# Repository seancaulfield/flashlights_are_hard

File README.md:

flashlights_are_hard
====================

My primative attempts to design a flashlight that has more complicated features
than ON/OFF without completely pissing me off.

Unless otherwise specified, everything here is licensed under the Creative
Commons Attribution-ShareAlike License.

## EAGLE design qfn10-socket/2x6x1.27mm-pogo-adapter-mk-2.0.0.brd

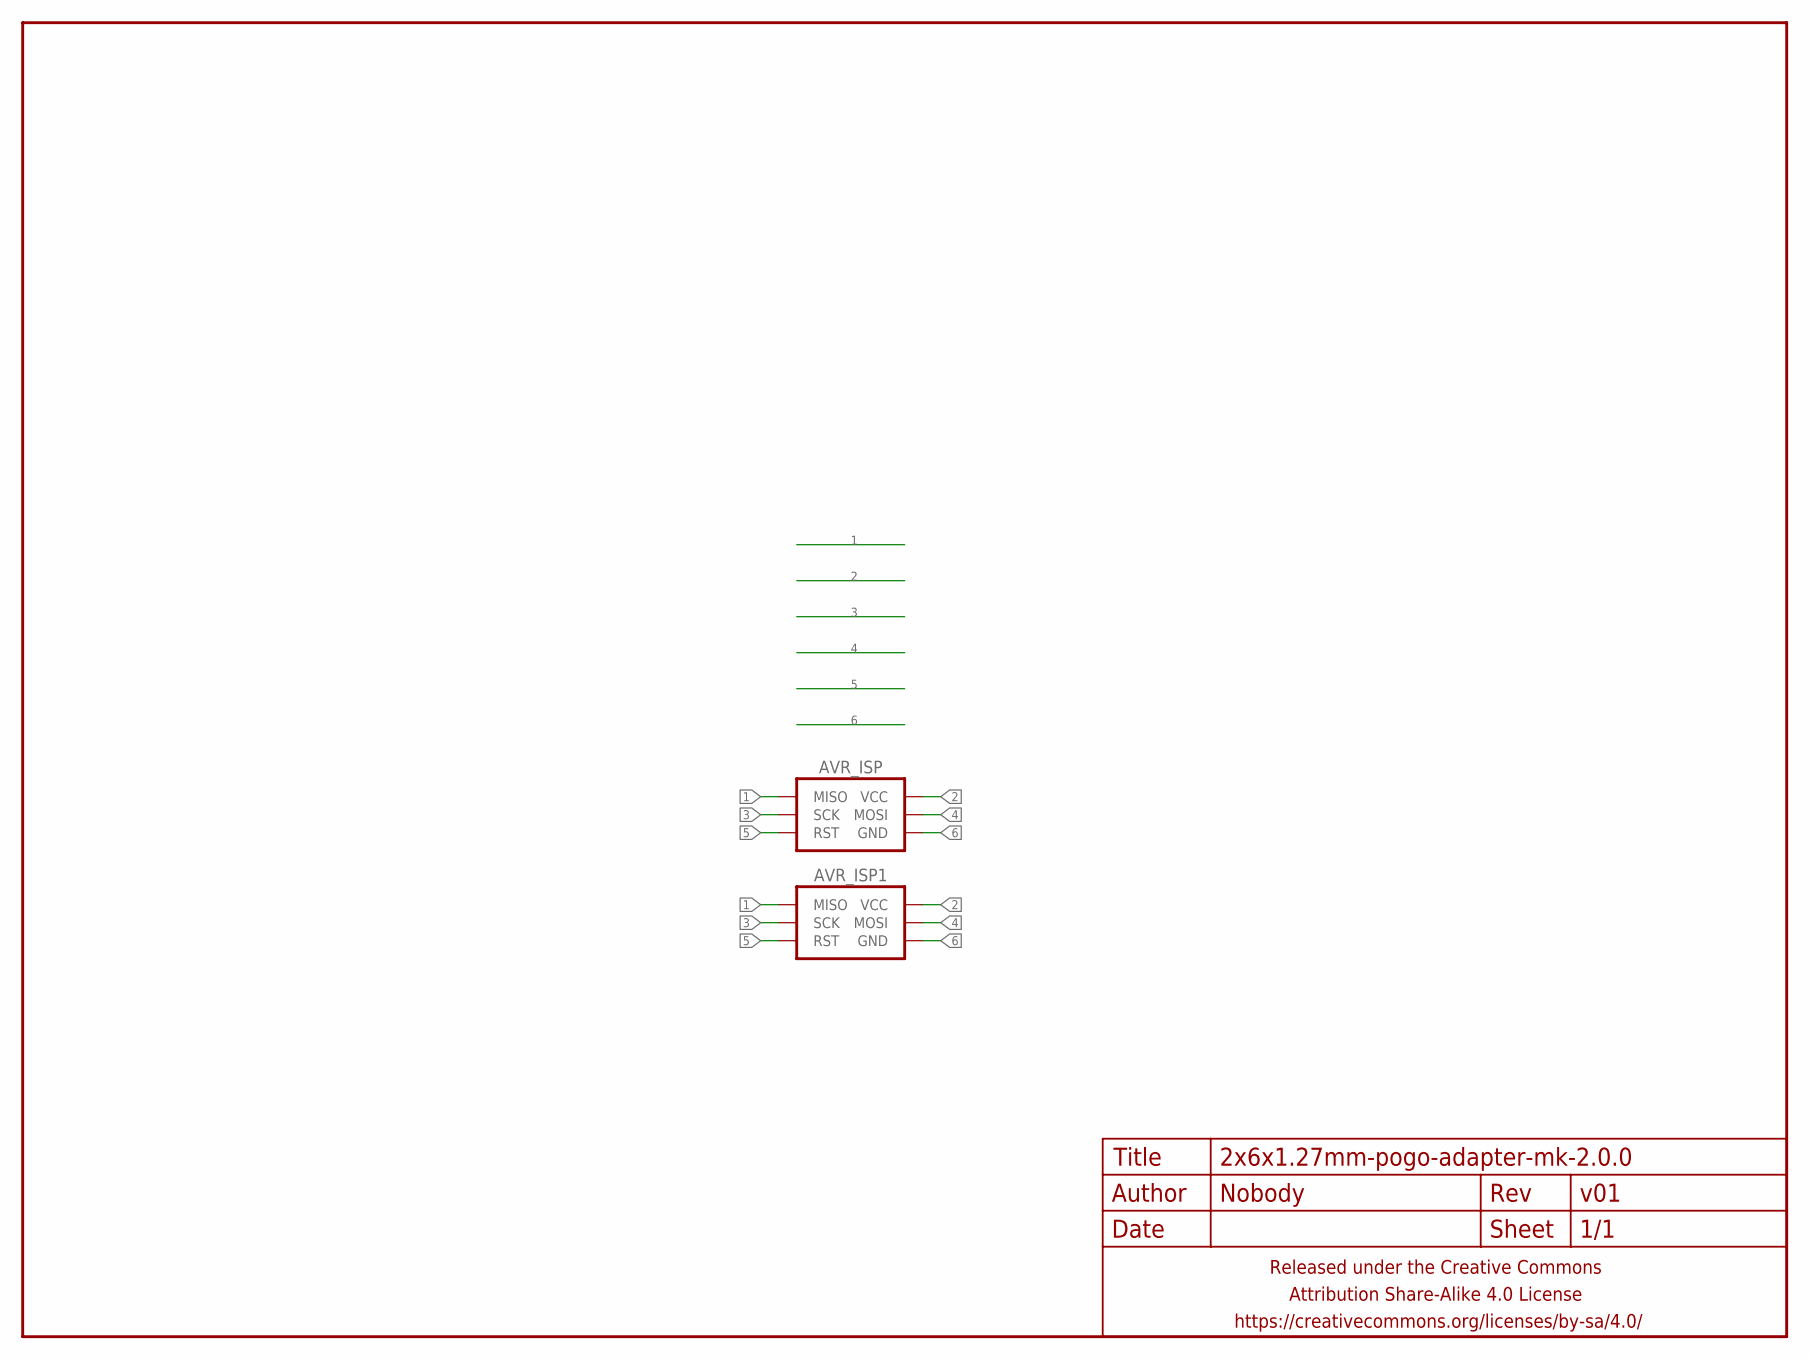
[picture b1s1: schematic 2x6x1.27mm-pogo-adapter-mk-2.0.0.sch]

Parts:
AVR_ISP: AVR_SPI_PRG_6SMD_POGO_POGO_POGO_BOUNCE_AVRISP; 2X3_SMD_POGO_RA_NARROW_AVRISP
AVR_ISP1: AVR_SPI_PRG_6PTH; 2X3
FRAME1: FRAME-LETTERNO_PACKAGE; DUMMY

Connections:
1: AVR_ISP.1@1 (MISO), AVR_ISP.1@2 (MISO), AVR_ISP1.1 (MISO)
2: AVR_ISP.2@1 (VCC), AVR_ISP.2@2 (VCC), AVR_ISP1.2 (VCC)
3: AVR_ISP.3@1 (SCK), AVR_ISP.3@2 (SCK), AVR_ISP1.3 (SCK)
4: AVR_ISP.4@1 (MOSI), AVR_ISP.4@2 (MOSI), AVR_ISP1.4 (MOSI)
5: AVR_ISP.5@1 (RST), AVR_ISP.5@2 (RST), AVR_ISP1.5 (RST)
6: AVR_ISP.6@1 (GND), AVR_ISP.6@2 (GND), AVR_ISP1.6 (GND)

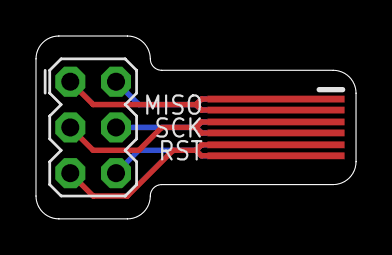
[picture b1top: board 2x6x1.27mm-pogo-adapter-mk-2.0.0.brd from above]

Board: 2 copper layers, 17.8 x 10.2 mm, 3 parts (0 on the bottom side), 6 nets.

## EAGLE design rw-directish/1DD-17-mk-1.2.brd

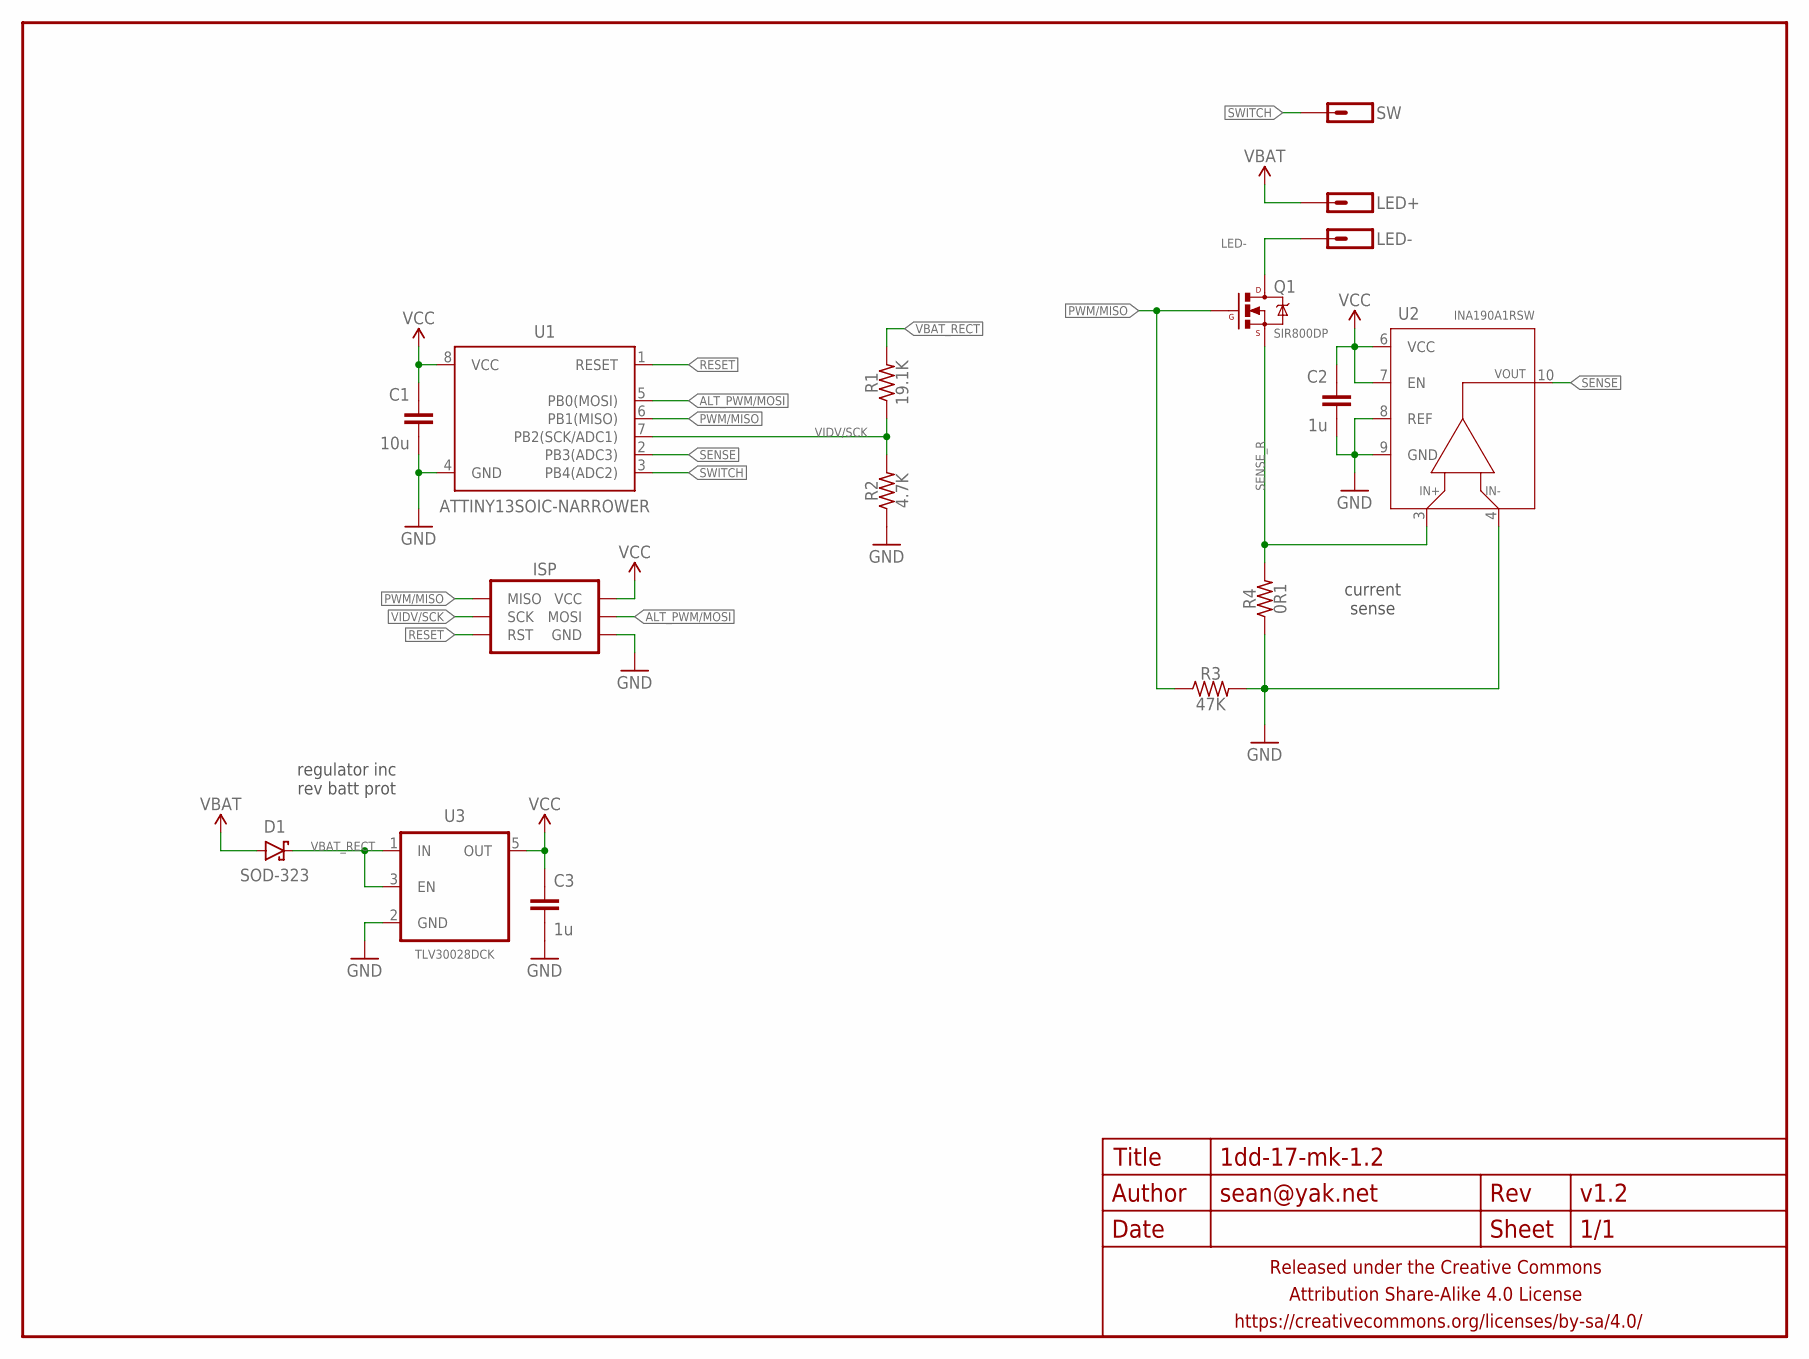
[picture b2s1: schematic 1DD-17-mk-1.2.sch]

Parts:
C1: 10u; C0402
C2, C3: 1u; C0402
D1: SOD-323; SOD323-SCHOTTKY
FRAME1: FRAME-LETTERNO_PACKAGE; DUMMY
ISP: AVR_SPI_PRG_6SMD-1.27MM; 2X3-1.27MM-SMD
LED+: M01PTH-0.9MM-CIR; 1X01-0.9MM-CIR
LED-: M01PTH-0.9MM-CIR; 1X01-0.9MM-CIR
Q1: SIR800DP; LFPAK56
R1: 19.1K; R0402
R2: 4.7K; R0402
R3: 47K; R0402
R4: 0R1; R0805-TIGHTER
SW: M01SMD-1MM-DIA-NS; 1X01-SMD-1MM-DIA-NS
U1: ATTINY13SOIC-NARROWER; SO08-SKINNYPADS
U2: INA190A1RSW; UQFN-10
U3: TLV30028DCK; SC70-TIGHTER

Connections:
ALT_PWM/MOSI: ISP.4 (MOSI), U1.5 (PB0(MOSI))
GND: C1.2, C2.2, C3.2, ISP.6 (GND), R2.1, R3.2, R4.1, U1.4 (GND), U2.4 (VIN-), U2.8 (REF), U2.9 (GND), U3.2 (GND)
LED-: LED-.P$1, Q1.PAD (D)
PWM/MISO: ISP.1 (MISO), Q1.4 (G), R3.1, U1.6 (PB1(MISO))
RESET: ISP.5 (RST), U1.1 (RESET)
SENSE: U1.2 (PB3(ADC3)), U2.10 (OUT)
SENSE_R: Q1.1 (S), Q1.2 (S), Q1.3 (S), R4.2, U2.3 (VIN+)
SWITCH: SW.P$1, U1.3 (PB4(ADC2))
VBAT: D1.A, LED+.P$1
VBAT_RECT: D1.C, R1.2, U3.1 (IN), U3.3 (EN)
VCC: C1.1, C2.1, C3.1, ISP.2 (VCC), U1.8 (VCC), U2.6 (VCC), U2.7 (EN), U3.5 (OUT)
VIDV/SCK: ISP.3 (SCK), R1.1, R2.2, U1.7 (PB2(SCK/ADC1))

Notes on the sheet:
current sense
regulator inc rev batt prot

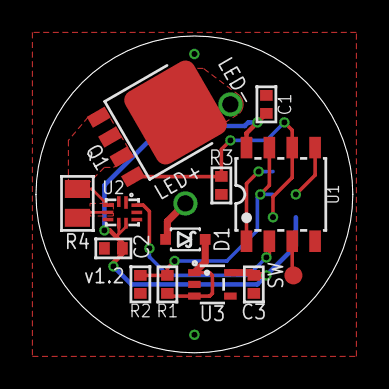
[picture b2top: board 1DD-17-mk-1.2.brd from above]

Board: 2 copper layers, 17.6 x 17.6 mm, 17 parts (1 on the bottom side), 12 nets.

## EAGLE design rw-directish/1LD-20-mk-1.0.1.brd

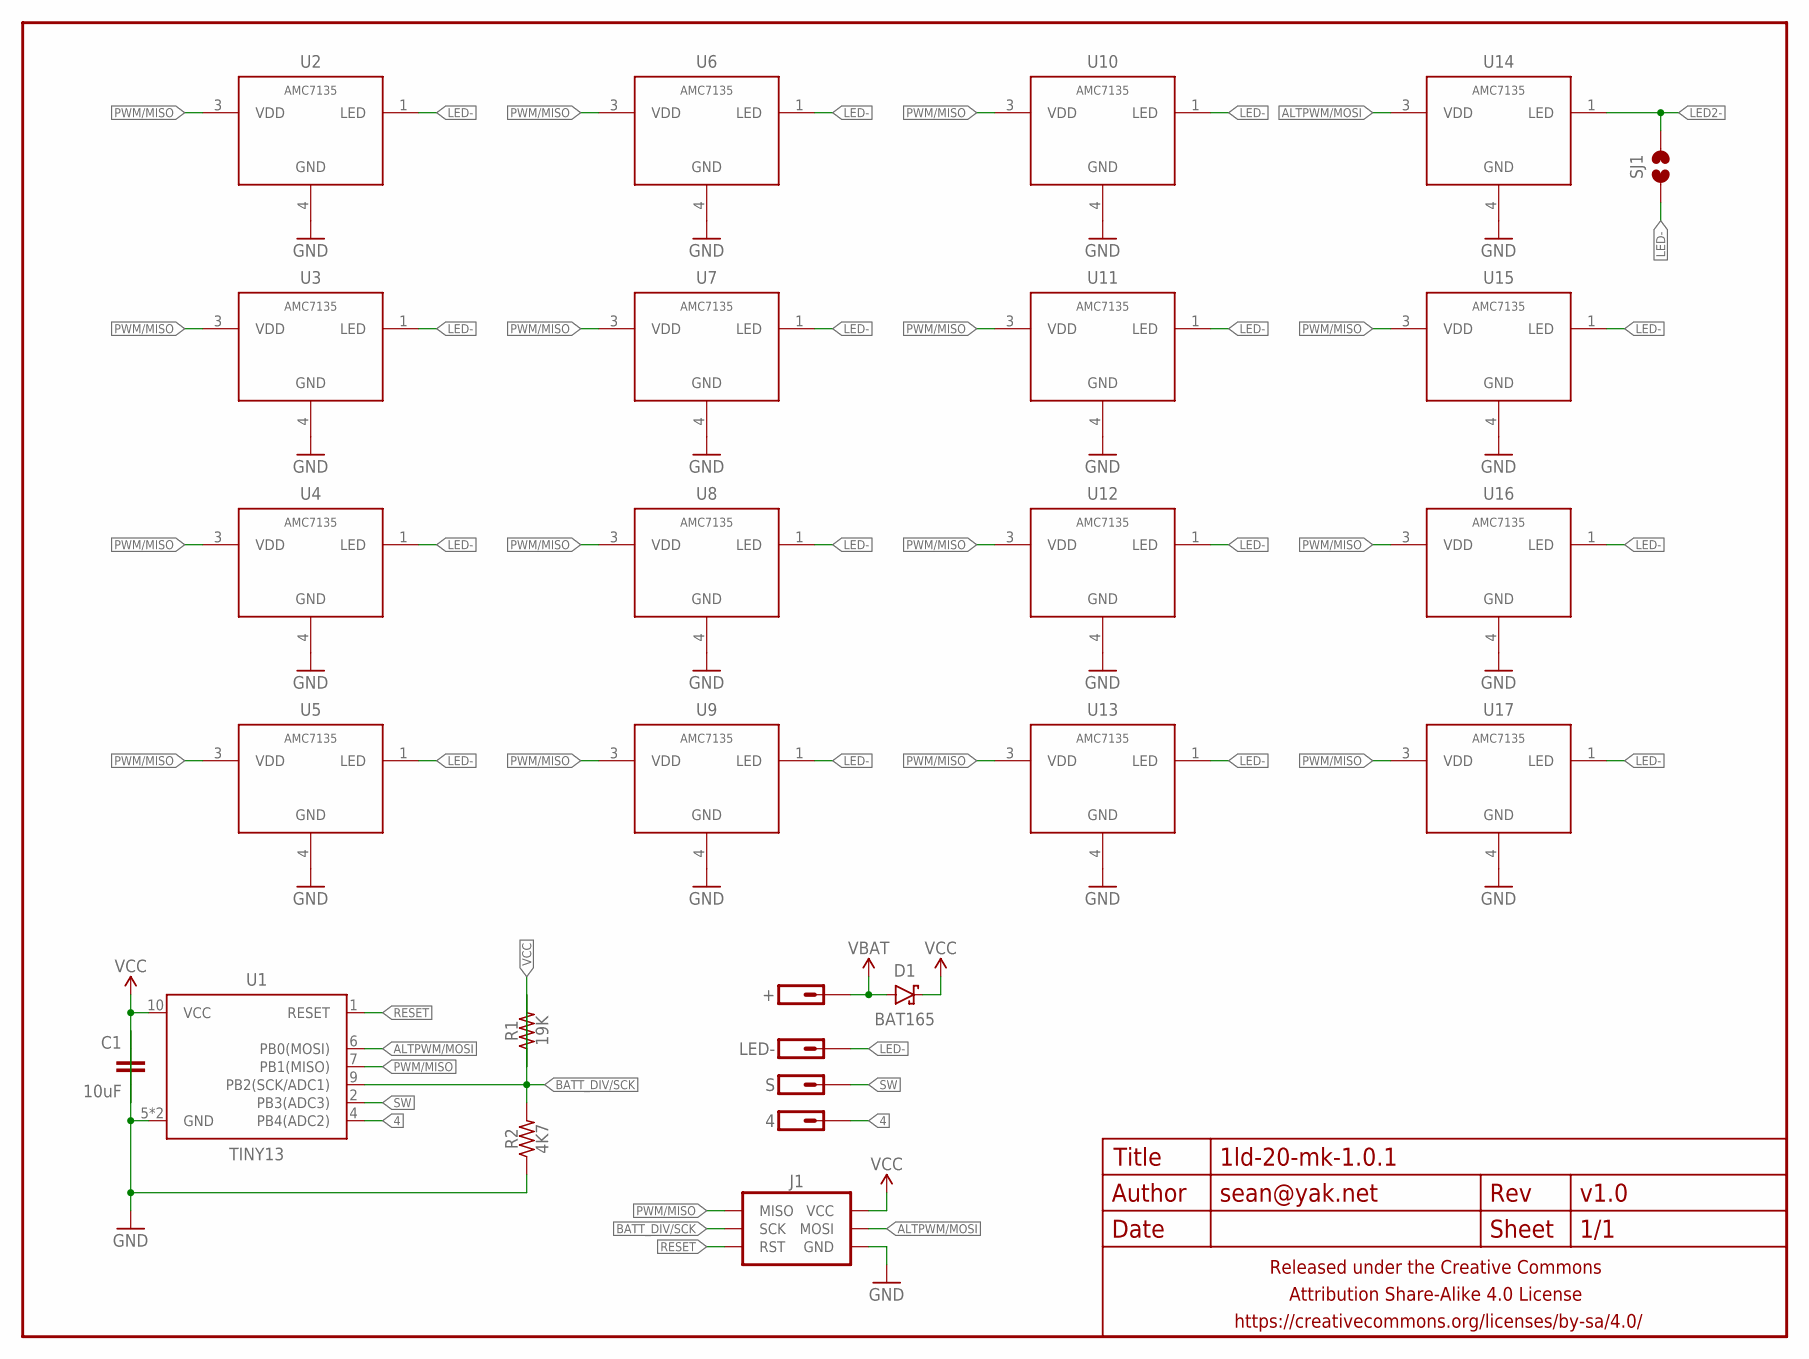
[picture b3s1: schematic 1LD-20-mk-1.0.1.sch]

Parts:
4: M01SMD-1MM-DIA-NS; 1X01-SMD-1MM-DIA-NS
+: M01PTH-1.4MM; 1X01-1.4MM-CIR
C1: 10uF; C0402
D1: BAT165; SOD323-SCHOTTKY
FRAME1: FRAME-LETTERNO_PACKAGE; DUMMY
J1: AVR_SPI_PRG_6SMD-1.27MM; 2X3-1.27MM-SMD
LED-: M01PTH-1MM-CIR-NS; 1X01-1MM-CIR-NS
R1: 19K; R0402
R2: 4K7; R0402
S: M01SMD-1MM-DIA-NS; 1X01-SMD-1MM-DIA-NS
SJ1: JUMPER-PAD-2-NOSMOL_NS; PAD-JUMPER-2-NO_SMOL_NS
U1: TINY13; QFN10(2X5)
U2, U3, U4, U5, U6, U7, U8, U9, U10, U11, U12, U13, U14, U15, U16, U17: AMC7135; SOT89-NOTHERM-ROUNDED-LESS

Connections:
4: 4.P$1, U1.4 (PB4(ADC2))
ALTPWM/MOSI: J1.4 (MOSI), U1.6 (PB0(MOSI)), U14.3 (VDD)
BATT_DIV/SCK: J1.3 (SCK), R1.2, R2.2, U1.9 (PB2(SCK/ADC1))
GND: C1.1, J1.6 (GND), R2.1, U1.5 (GND), U1.PAD (GND), U2.4 (GND), U3.4 (GND), U4.4 (GND), U5.4 (GND), U6.4 (GND), U7.4 (GND), U8.4 (GND), U9.4 (GND), U10.4 (GND), U11.4 (GND), U12.4 (GND), U13.4 (GND), U14.4 (GND), U15.4 (GND), U16.4 (GND), U17.4 (GND)
LED2-: SJ1.2, U14.1 (LED)
LED-: LED-.1, SJ1.1, U2.1 (LED), U3.1 (LED), U4.1 (LED), U5.1 (LED), U6.1 (LED), U7.1 (LED), U8.1 (LED), U9.1 (LED), U10.1 (LED), U11.1 (LED), U12.1 (LED), U13.1 (LED), U15.1 (LED), U16.1 (LED), U17.1 (LED)
PWM/MISO: J1.1 (MISO), U1.7 (PB1(MISO)), U2.3 (VDD), U3.3 (VDD), U4.3 (VDD), U5.3 (VDD), U6.3 (VDD), U7.3 (VDD), U8.3 (VDD), U9.3 (VDD), U10.3 (VDD), U11.3 (VDD), U12.3 (VDD), U13.3 (VDD), U15.3 (VDD), U16.3 (VDD), U17.3 (VDD)
RESET: J1.5 (RST), U1.1 (RESET)
SW: S.P$1, U1.2 (PB3(ADC3))
VBAT: +.P$1, D1.A
VCC: C1.2, D1.C, J1.2 (VCC), R1.1, U1.10 (VCC)

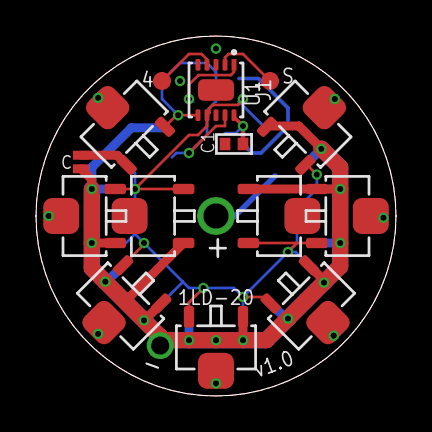
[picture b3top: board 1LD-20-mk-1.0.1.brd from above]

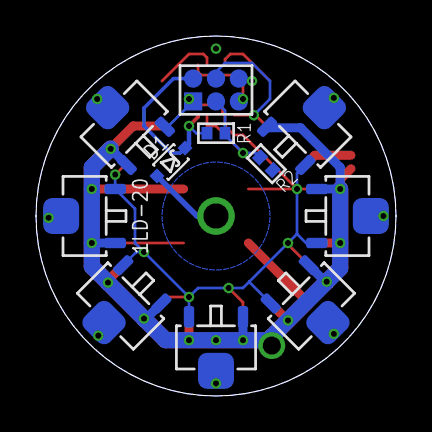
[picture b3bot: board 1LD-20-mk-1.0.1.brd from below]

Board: 2 copper layers, 20.0 x 20.0 mm, 28 parts (11 on the bottom side), 11 nets.

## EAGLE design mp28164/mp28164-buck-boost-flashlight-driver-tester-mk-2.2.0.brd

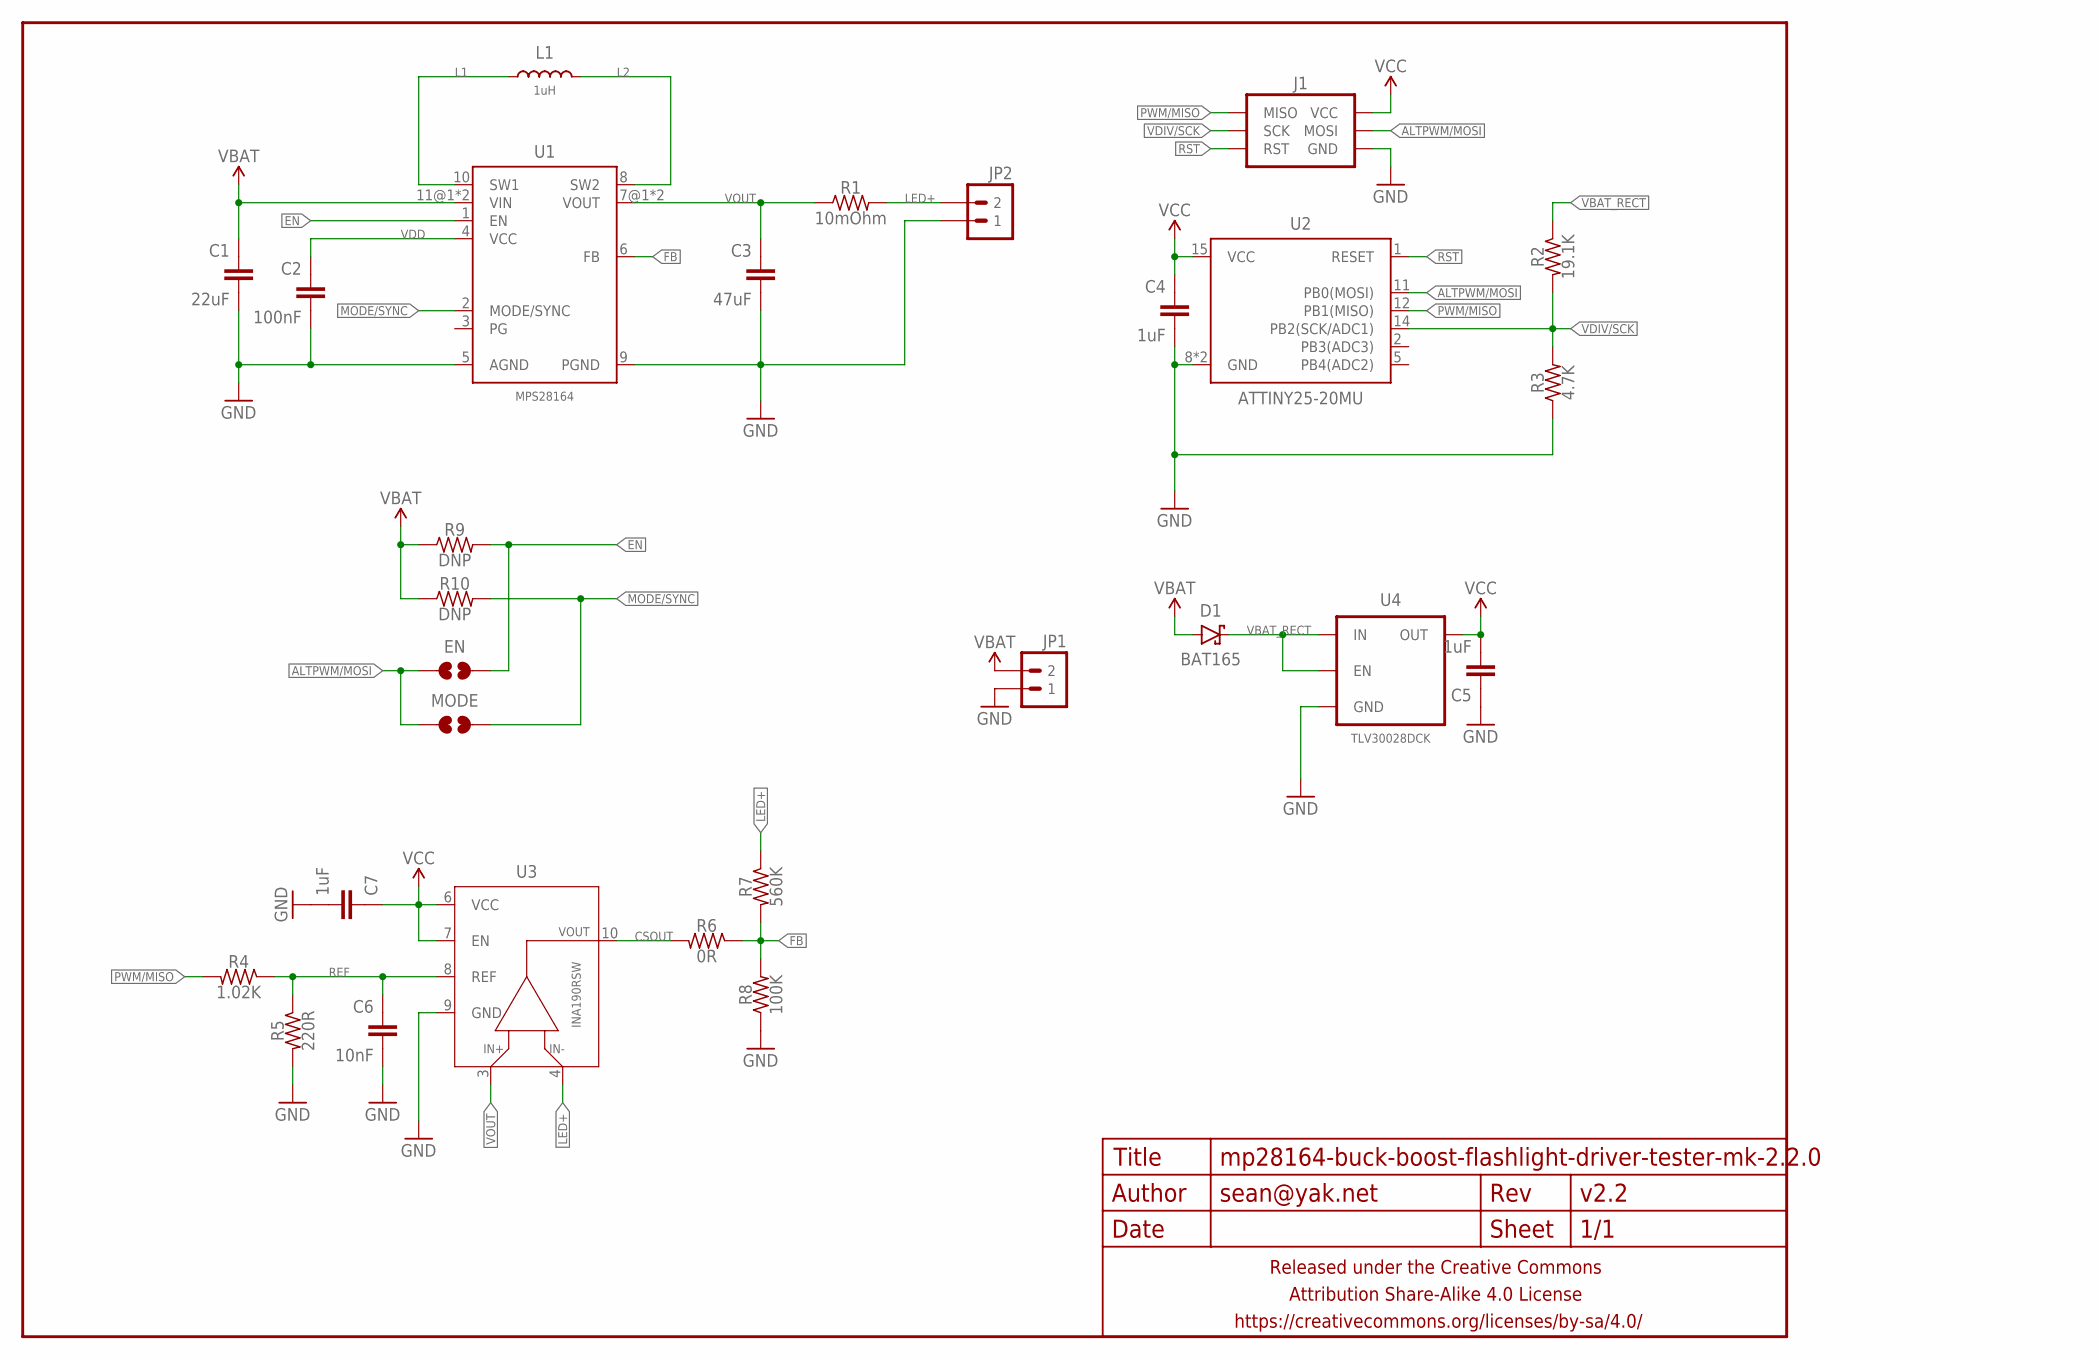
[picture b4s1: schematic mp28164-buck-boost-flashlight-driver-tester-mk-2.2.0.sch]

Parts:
C1: 22uF; C1206
C2: 100nF; C0402
C3: 47uF; C1206
C4, C5, C7: 1uF; C0402
C6: 10nF; C0402
D1: BAT165; SOD323-SCHOTTKY
EN: JUMPER-PAD-2-NOYES_SILK; PAD-JUMPER-2-NO_YES_SILK
FRAME1: FRAME-LETTERNO_PACKAGE; DUMMY
J1: AVR_SPI_PRG_6PTH; 2X3
JP1, JP2: M021X02_NO_SILK; 1X02_NO_SILK
L1: 1uH; XAL60XX
MODE: JUMPER-PAD-2-NOYES_SILK; PAD-JUMPER-2-NO_YES_SILK
R1: 10mOhm; R1206
R2: 19.1K; R0402
R3: 4.7K; R0402
R4: 1.02K; R0402
R5: 220R; R0402
R6: 0R; R0402
R7: 560K; R0402
R8: 100K; R0402
R9, R10: DNP; R0402
U1: MPS28164
U2: ATTINY25-20MU; QFN20
U3: INA190RSW; UQFN-10
U4: TLV30028DCK; SC70-TIGHTER

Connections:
ALTPWM/MOSI: EN.1, J1.4 (MOSI), MODE.1, U2.11 (PB0(MOSI))
CSOUT: R6.2, U3.10 (OUT)
EN: EN.2, R9.2, U1.1 (EN)
FB: R6.1, R7.2, R8.2, U1.6 (FB)
GND: C1.2, C2.2, C3.2, C4.2, C5.1, C6.2, C7.2, J1.6 (GND), JP1.1, JP2.1, R3.1, R5.2, R8.1, U1.5 (AGND), U1.9 (PGND), U2.8 (GND), U2.PAD (GND), U3.9 (GND), U4.2 (GND)
L1: L1.P$1 (1), U1.10 (SW1)
L2: L1.P$2 (2), U1.8 (SW2)
LED+: JP2.2, R1.2, R7.1, U3.4 (VIN-)
MODE/SYNC: MODE.2, R10.2, U1.2 (MODE/SYNC)
PWM/MISO: J1.1 (MISO), R4.2, U2.12 (PB1(MISO))
REF: C6.1, R4.1, R5.1, U3.8 (REF)
RST: J1.5 (RST), U2.1 (RESET)
VBAT: C1.1, D1.A, JP1.2, R9.1, R10.1, U1.11@1 (VIN), U1.11@2 (VIN)
VBAT_RECT: D1.C, R2.1, U4.1 (IN), U4.3 (EN)
VCC: C4.1, C5.2, C7.1, J1.2 (VCC), U2.15 (VCC), U3.6 (VCC), U3.7 (EN), U4.5 (OUT)
VDD: C2.1, U1.4 (VCC)
VDIV/SCK: J1.3 (SCK), R2.2, R3.2, U2.14 (PB2(SCK/ADC1))
VOUT: C3.1, R1.1, U1.7@1 (VOUT), U1.7@2 (VOUT), U3.3 (VIN+)

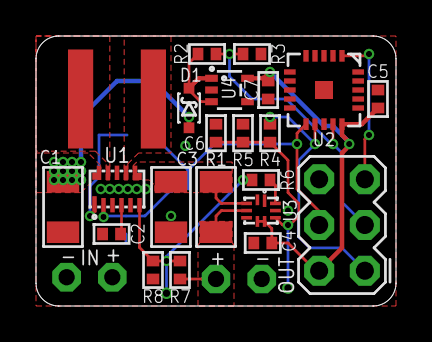
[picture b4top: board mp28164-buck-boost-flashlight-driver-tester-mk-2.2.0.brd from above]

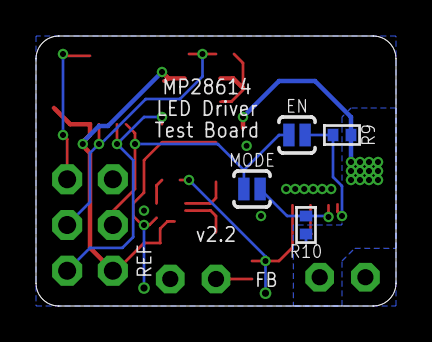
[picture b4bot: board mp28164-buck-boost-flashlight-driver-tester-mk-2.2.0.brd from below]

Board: 2 copper layers, 20.0 x 15.0 mm, 29 parts (4 on the bottom side), 18 nets.

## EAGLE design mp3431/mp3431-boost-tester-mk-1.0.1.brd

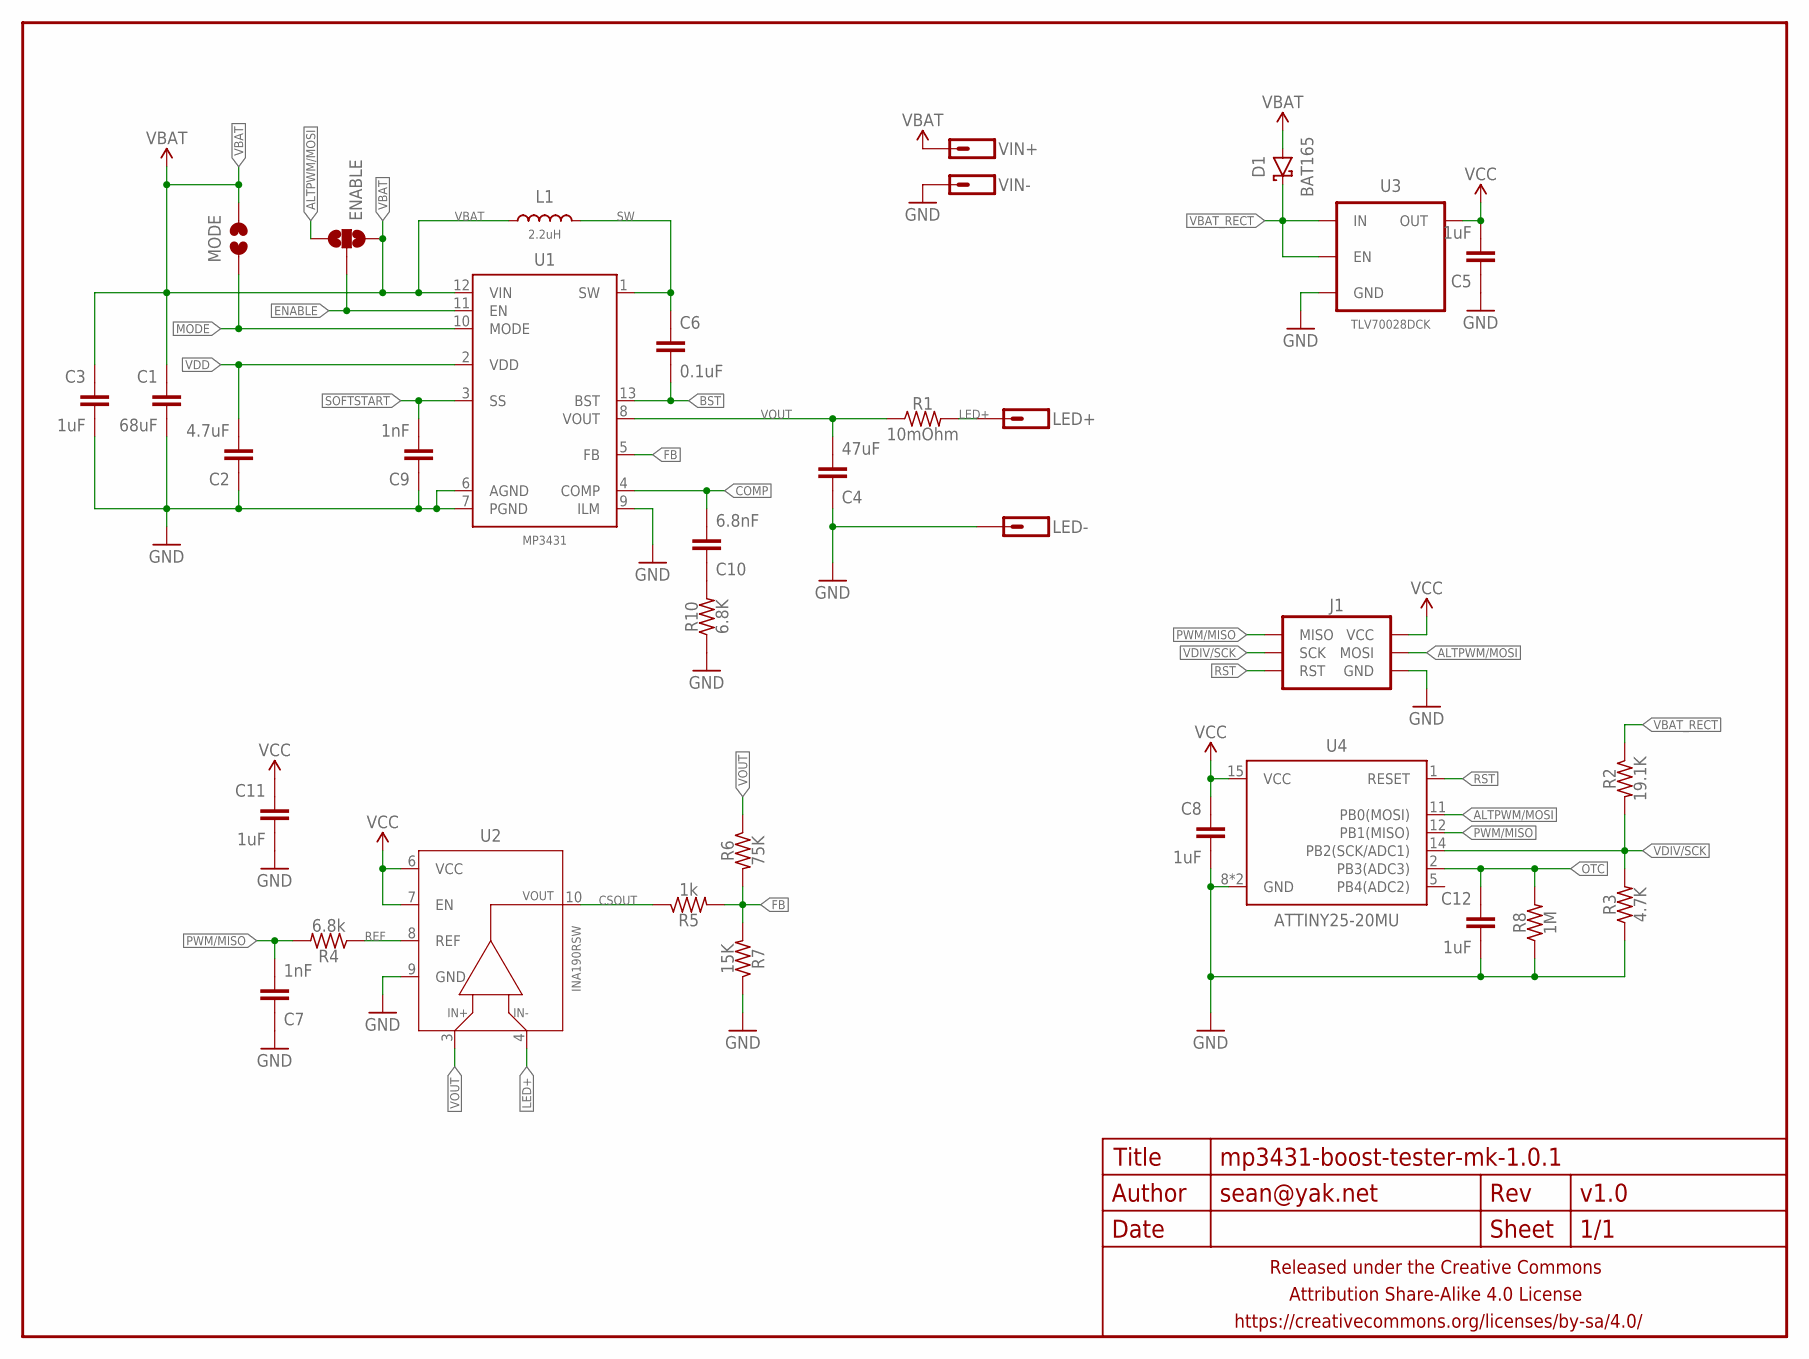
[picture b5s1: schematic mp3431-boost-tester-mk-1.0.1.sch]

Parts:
C1: 68uF; C1210
C2: 4.7uF; C0402
C3, C5, C8, C11, C12: 1uF; C0402
C4: 47uF; C1210
C6: 0.1uF; C0402
C7, C9: 1nF; C0402
C10: 6.8nF; C0402
D1: BAT165; SOD323-SCHOTTKY
ENABLE: JUMPER-PAD-3-NOSMALL_BOX_SILK; PAD-JUMPER-3-NO_YES_SILK_SMALL_BOX
FRAME1: FRAME-LETTERNO_PACKAGE; DUMMY
J1: AVR_SPI_PRG_6PTH; 2X3
L1: 2.2uH; XAL7070
LED+: M01PTH-1.2MM-NS; 1X01-1.2MM-NS
LED-: M01PTH-1.2MM-NS; 1X01-1.2MM-NS
MODE: JUMPER-PAD-2-NOYES_SILK; PAD-JUMPER-2-NO_YES_SILK
R1: 10mOhm; R1206
R2: 19.1K; R0402
R3: 4.7K; R0402
R4: 6.8k; R0402
R5: 1k; R0402
R6: 75K; R0402
R7: 15K; R0402
R8: 1M; R0402
R10: 6.8K; R0402
U1: MP3431
U2: INA190RSW; UQFN-10
U3: TLV70028DCK; SC70
U4: ATTINY25-20MU; QFN20
VIN+: M01PTH-1.2MM-NS; 1X01-1.2MM-NS
VIN-: M01PTH-1.2MM-NS; 1X01-1.2MM-NS

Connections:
ALTPWM/MOSI: ENABLE.3, J1.4 (MOSI), U4.11 (PB0(MOSI))
BST: C6.2, U1.13 (BST)
COMP: C10.2, U1.4 (COMP)
COMP_MID: C10.1, R10.2
CSOUT: R5.1, U2.10 (OUT)
ENABLE: ENABLE.2, U1.11 (EN)
FB: R5.2, R6.2, R7.2, U1.5 (FB)
GND: C1.2, C2.1, C3.2, C4.1, C5.1, C7.1, C8.2, C9.1, C11.2, C12.2, J1.6 (GND), LED-.P$1, R3.1, R7.1, R8.1, R10.1, U1.6 (AGND), U1.7 (PGND), U1.9 (ILM), U2.9 (GND), U3.2 (GND), U4.8 (GND), U4.PAD (GND), VIN-.P$1
LED+: LED+.P$1, R1.2, U2.4 (VIN-)
MODE: MODE.1, U1.10 (MODE)
OTC: C12.1, R8.2, U4.2 (PB3(ADC3))
PWM/MISO: C7.2, J1.1 (MISO), R4.2, U4.12 (PB1(MISO))
REF: R4.1, U2.8 (REF)
RST: J1.5 (RST), U4.1 (RESET)
SOFTSTART: C9.2, U1.3 (SS)
SW: C6.1, L1.P$2 (2), U1.1 (SW)
VBAT: C1.1, C3.1, D1.A, ENABLE.1, L1.P$1 (1), MODE.2, U1.12 (VIN), VIN+.P$1
VBAT_RECT: D1.C, R2.1, U3.1 (IN), U3.3 (EN)
VCC: C5.2, C8.1, C11.1, J1.2 (VCC), U2.6 (VCC), U2.7 (EN), U3.5 (OUT), U4.15 (VCC)
VDD: C2.2, U1.2 (VDD)
VDIV/SCK: J1.3 (SCK), R2.2, R3.2, U4.14 (PB2(SCK/ADC1))
VOUT: C4.2, R1.1, R6.1, U1.8 (VOUT), U2.3 (VIN+)

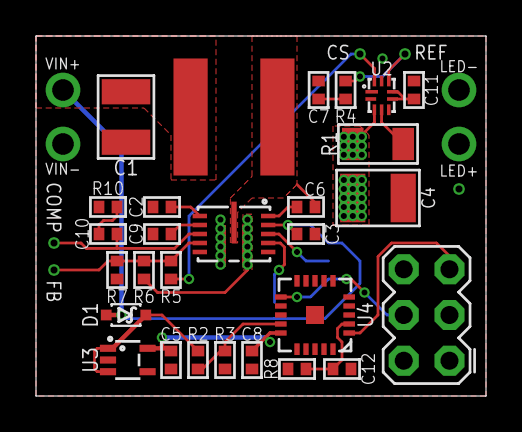
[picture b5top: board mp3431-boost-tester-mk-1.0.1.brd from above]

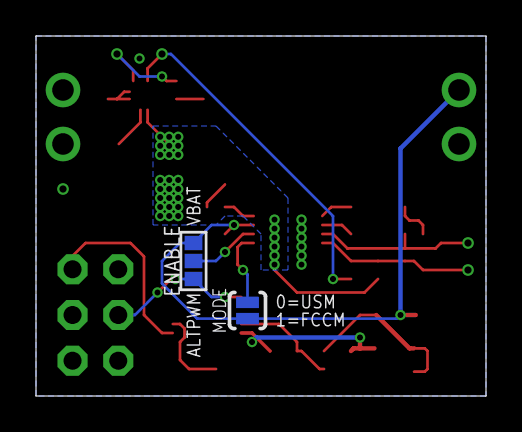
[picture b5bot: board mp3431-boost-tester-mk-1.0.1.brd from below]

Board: 2 copper layers, 25.0 x 20.0 mm, 35 parts (2 on the bottom side), 22 nets.

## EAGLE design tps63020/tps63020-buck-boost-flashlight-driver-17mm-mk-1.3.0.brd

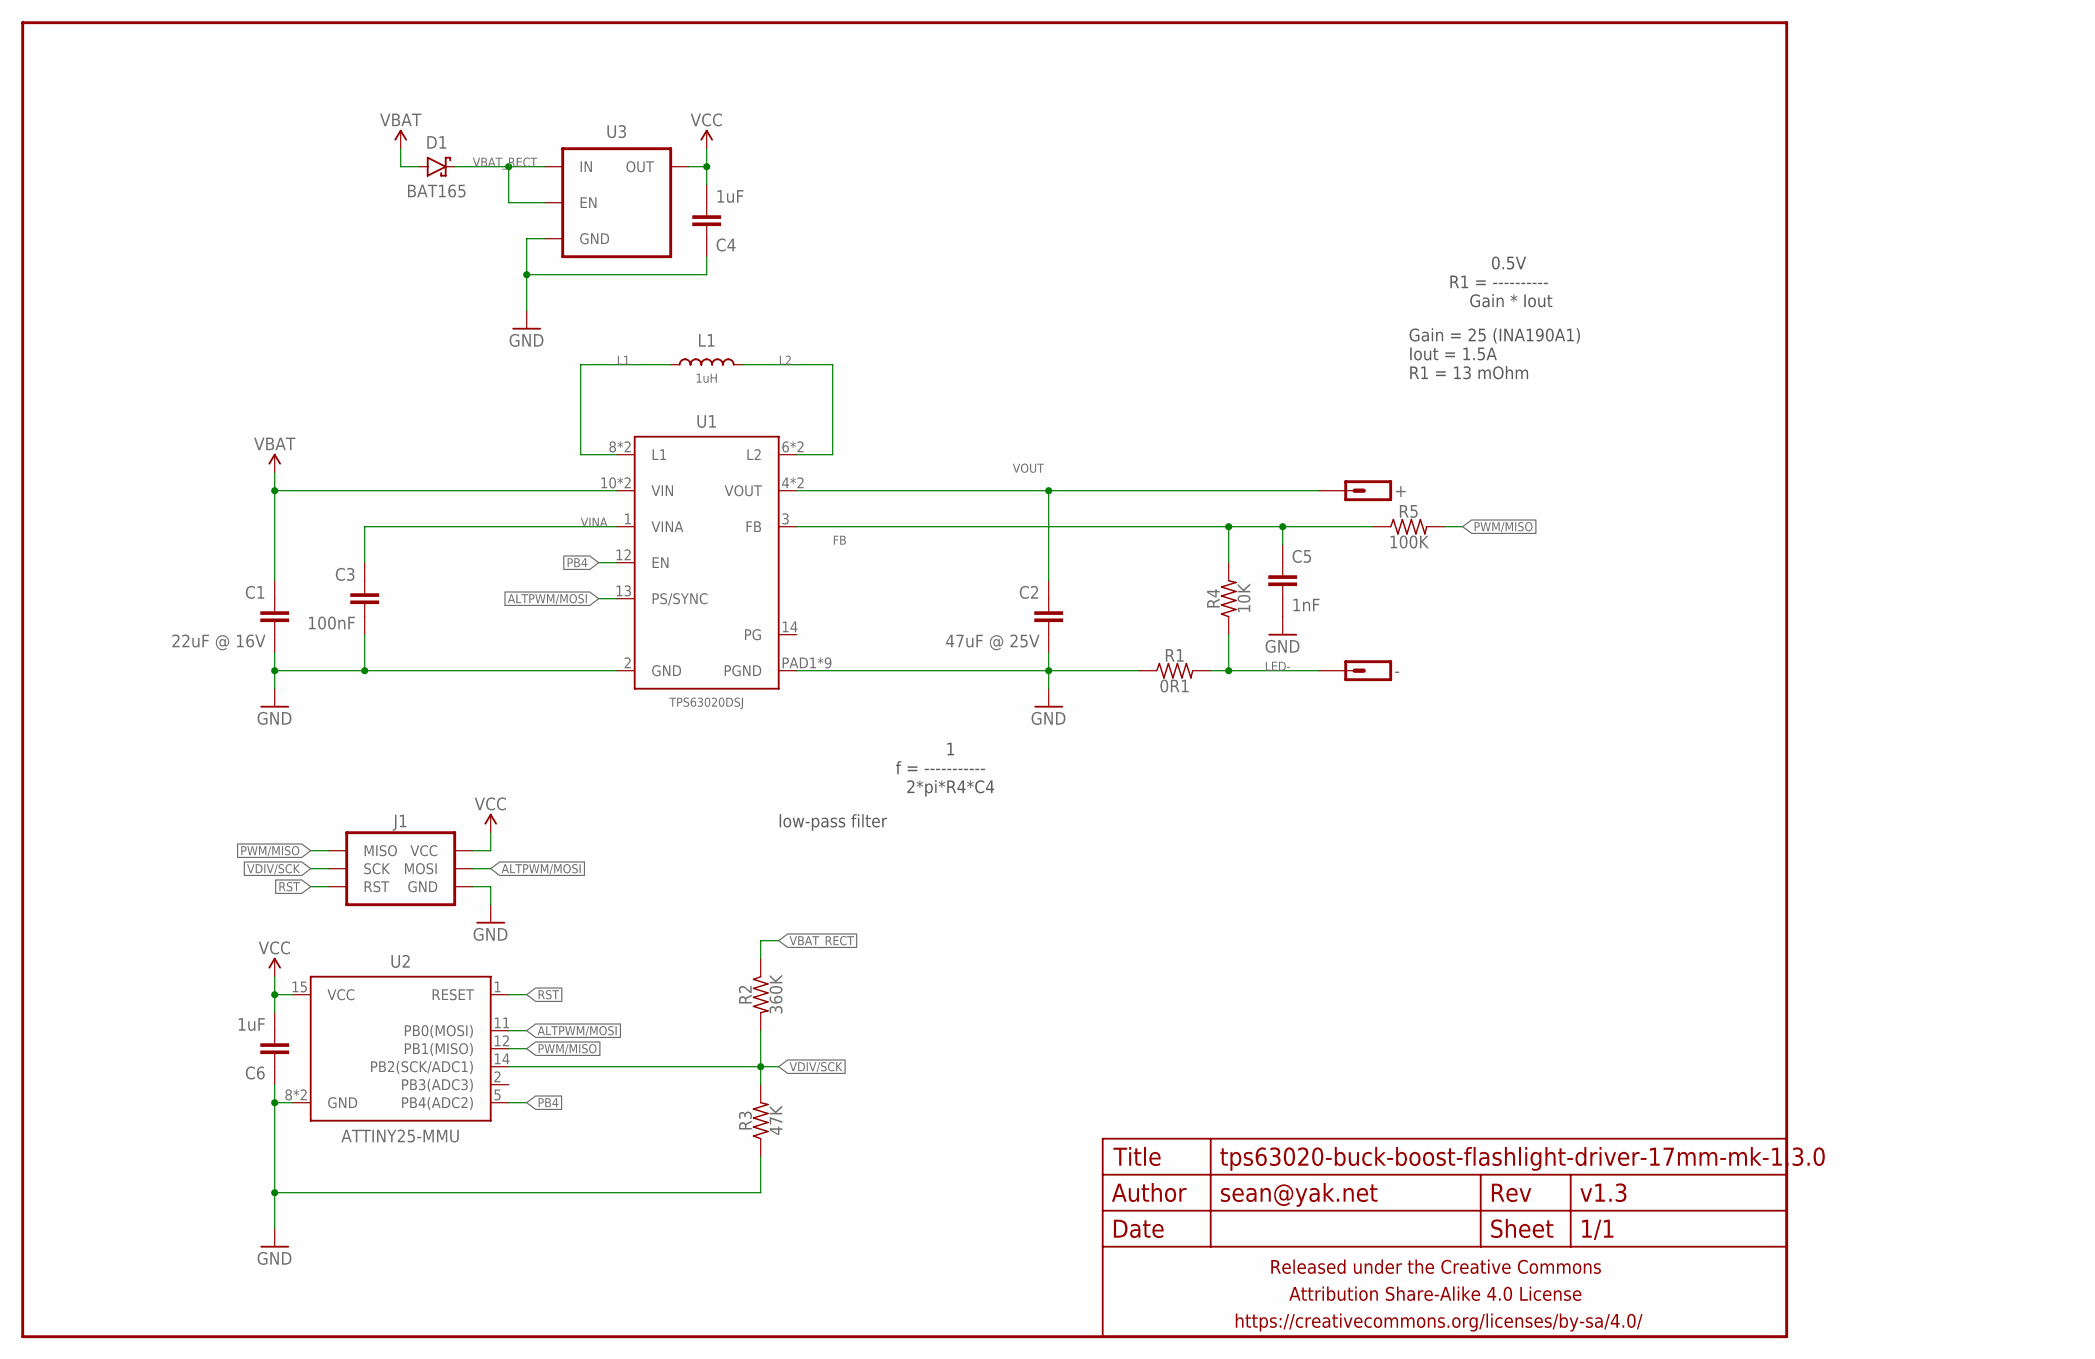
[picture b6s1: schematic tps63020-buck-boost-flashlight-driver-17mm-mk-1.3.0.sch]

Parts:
+: M01SMD-1.6MMX3.2MM; 1X01-SMD-1.6MMX3.2MM
-: M01SMD-1.6MMX3.2MM; 1X01-SMD-1.6MMX3.2MM
C1: 22uF @ 16V; C0805-TIGHTER
C2: 47uF @ 25V; C1206
C3: 100nF; C0402
C4, C6: 1uF; C0402
C5: 1nF; C0402
D1: BAT165; SOD323-SCHOTTKY
FRAME1: FRAME-LETTERNO_PACKAGE; DUMMY
J1: AVR_SPI_PRG_6SMD-1.27MM; 2X3-1.27MM-SMD
L1: 1uH; XAL50X0
R1: 0R1; R1206
R2: 360K; R0402
R3: 47K; R0402
R4: 10K; R0402
R5: 100K; R0402
U1: TPS63020DSJ; VSON-14-4MMX3MM
U2: ATTINY25-MMU; QFN20
U3: V_REG_ENTLV700XXDCK-TIGHTER; SC70-TIGHTER

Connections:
ALTPWM/MOSI: J1.4 (MOSI), U1.13 (PS/SYNC), U2.11 (PB0(MOSI))
FB: C5.1, R4.2, R5.1, U1.3 (FB)
GND: C1.2, C2.2, C3.2, C4.1, C5.2, C6.1, J1.6 (GND), R1.1, R3.1, U1.2 (GND), U1.PAD1 (PGND), U1.PAD2 (PGND), U1.PAD3 (PGND), U1.PAD4 (PGND), U1.PAD5 (PGND), U1.PAD6 (PGND), U1.PAD7 (PGND), U1.PAD8 (PGND), U1.PADCENTER (PGND), U2.8 (GND), U2.PAD (GND), U3.2 (GND)
L1: L1.P$1 (1), U1.8 (L1), U1.9 (L1)
L2: L1.P$2 (2), U1.6 (L2), U1.7 (L2)
LED-: -.P$1, R1.2, R4.1
PB4: U1.12 (EN), U2.5 (PB4(ADC2))
PWM/MISO: J1.1 (MISO), R5.2, U2.12 (PB1(MISO))
RST: J1.5 (RST), U2.1 (RESET)
VBAT: C1.1, D1.A, U1.10 (VIN), U1.11 (VIN)
VBAT_RECT: D1.C, R2.1, U3.1 (IN), U3.3 (EN)
VCC: C4.2, C6.2, J1.2 (VCC), U2.15 (VCC), U3.5 (OUT)
VDIV/SCK: J1.3 (SCK), R2.2, R3.2, U2.14 (PB2(SCK/ADC1))
VINA: C3.1, U1.1 (VINA)
VOUT: +.P$1, C2.1, U1.4 (VOUT), U1.5 (VOUT)

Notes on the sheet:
1 f = ----------- 2*pi*R4*C4
0.5V R1 = ---------- Gain * Iout
low-pass filter
Gain = 25 (INA190A1) Iout = 1.5A R1 = 13 mOhm

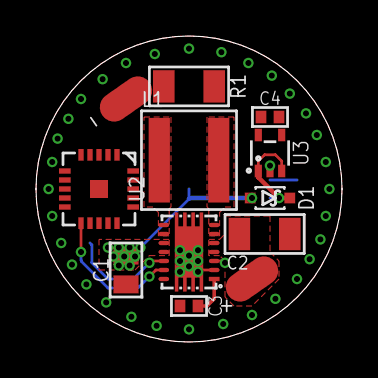
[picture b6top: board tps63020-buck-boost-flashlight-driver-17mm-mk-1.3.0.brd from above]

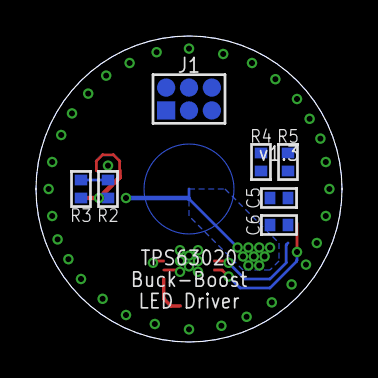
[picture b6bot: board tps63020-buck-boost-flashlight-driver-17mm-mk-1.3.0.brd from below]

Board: 2 copper layers, 17.0 x 17.0 mm, 20 parts (7 on the bottom side), 15 nets.

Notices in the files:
parts and their libraries:
a_parts: Released under the Creative Commons Attribution Share-Alike 4.0 License
a_parts: https://creativecommons.org/licenses/by-sa/4.0
a_parts: Released under the Creative Commons
